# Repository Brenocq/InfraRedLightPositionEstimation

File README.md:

# Light Position Estimation

## Introduction
This project aims to create a neural network to estimate the position of a light emitting object using multiple light sensors.
Firstly the tests are being performed using visible light. In the next step I will use infrared light emitters and receivers.
The main motivation for this project is to allow low cost robots to locate the position of other robots relative to them.

## The Neural Network
Starting from the scenario where there are several robots emitting light and reading the light intensity of the environment. My goal is to get each robot to be able to determine the relative position of another robot using only light sensors. The neural network input will be the reading of each sensor, while the output will be the relative coordinate of the other robot closest to it.

### Training
The training will take place using a camera to detect the relative position of the _light emitting PCB_ relative to the _main PCB with sensors_. After data is collected, the neural network is fed with the values of each sensor and the error is adjusted using the coordinates of the robots.

## Experiments
### First experiment: Visible light

#### Work in progress...

### Installation
```
sudo apt-get install libusb-1.0-0.dev
sudo apt-get install libboost-all-dev
sudo apt-get install cmake

cd LightPositionEstimation/src/Raspberry/lib/Pixy/
rm -r build
cd scripts
./build_libpixyusb.sh
./install_libpixyusb.sh

cd ../../../
rm -r build
./make.sh
```

[Pixymon](https://docs.pixycam.com/wiki/doku.php?id=wiki:v1:installing_pixymon_on_linux)

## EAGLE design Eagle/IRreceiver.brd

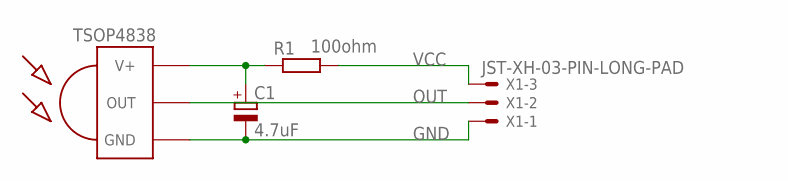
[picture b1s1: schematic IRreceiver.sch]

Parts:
C1: 4.7uF; 153CLV-0405
R1: 100ohm; R0805
U$1: TSOP4838; TSOP18XX
X1: JST-XH-03-PIN-LONG-PAD; JST-XH-03-PACKAGE-LONG-PAD

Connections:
GND: C1.-, U$1.GND, X1.1
unnamed: C1.+, R1.1, U$1.VCC (V+)
OUT: U$1.OUT, X1.2
VCC: R1.2, X1.3

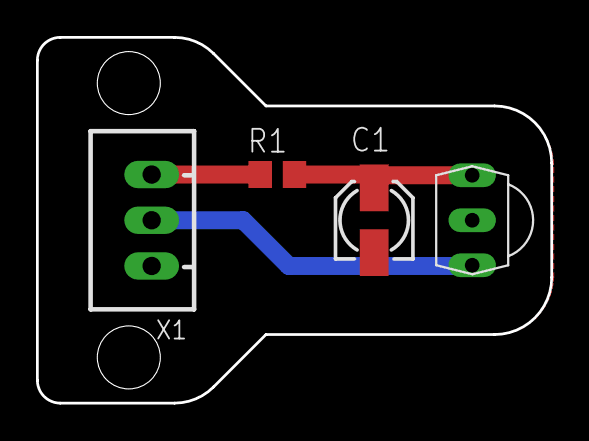
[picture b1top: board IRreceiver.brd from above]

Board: 2 copper layers, 28.6 x 20.3 mm, 4 parts (0 on the bottom side), 4 nets.

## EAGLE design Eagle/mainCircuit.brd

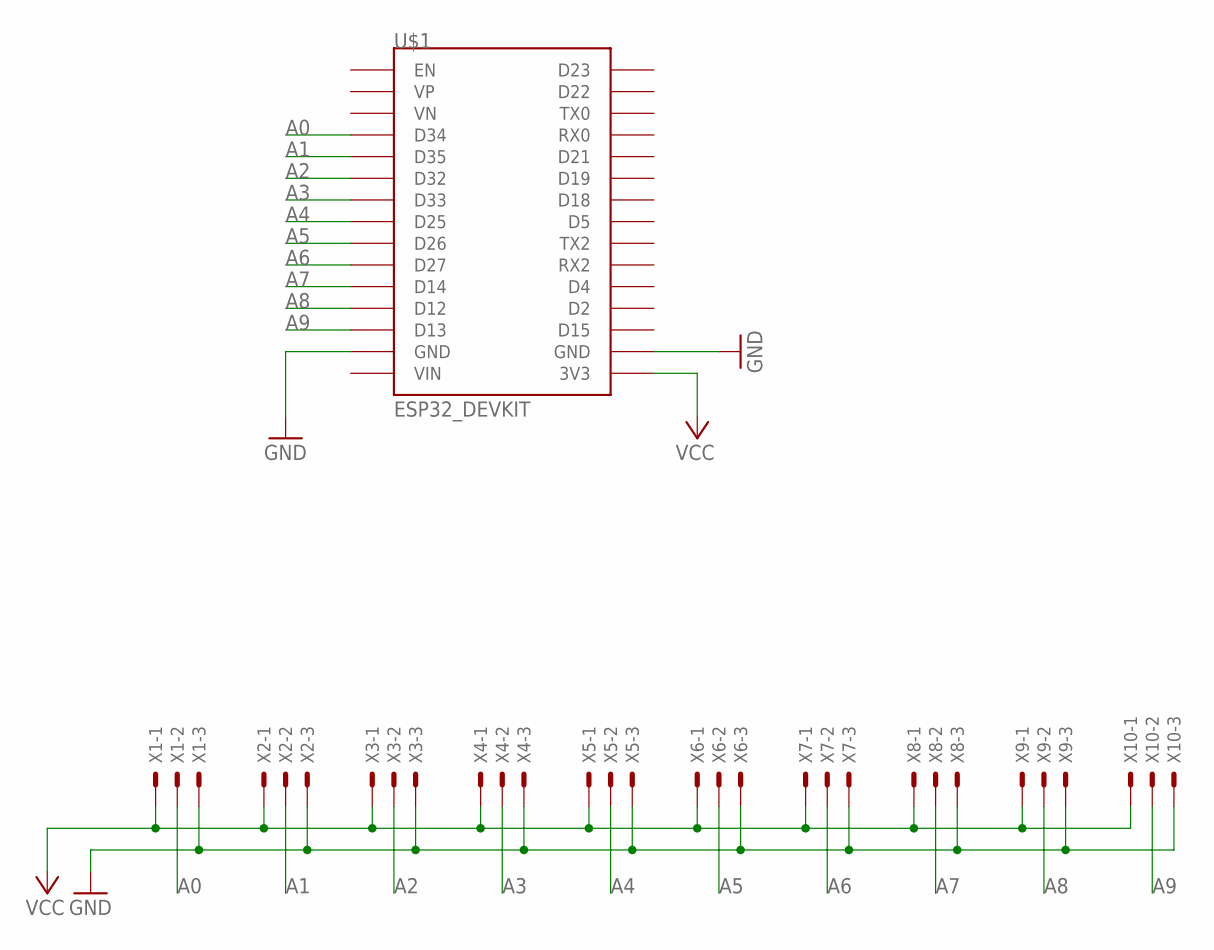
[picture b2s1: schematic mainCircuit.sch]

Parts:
U$1: ESP32_DEVKIT
X1, X2, X3, X4, X5, X6, X7, X8, X9, X10: JST-XH-03-PIN-LONG-PAD; JST-XH-03-PACKAGE-LONG-PAD

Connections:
A0: U$1.D34, X1.2
A1: U$1.D35, X2.2
A2: U$1.D32, X3.2
A3: U$1.D33, X4.2
A4: U$1.D25, X5.2
A5: U$1.D26, X6.2
A6: U$1.D27, X7.2
A7: U$1.D14, X8.2
A8: U$1.D12, X9.2
A9: U$1.D13, X10.2
GND: U$1.GND@1 (GND), U$1.GND@2 (GND), X1.3, X2.3, X3.3, X4.3, X5.3, X6.3, X7.3, X8.3, X9.3, X10.3
VCC: U$1.3V3, X1.1, X2.1, X3.1, X4.1, X5.1, X6.1, X7.1, X8.1, X9.1, X10.1

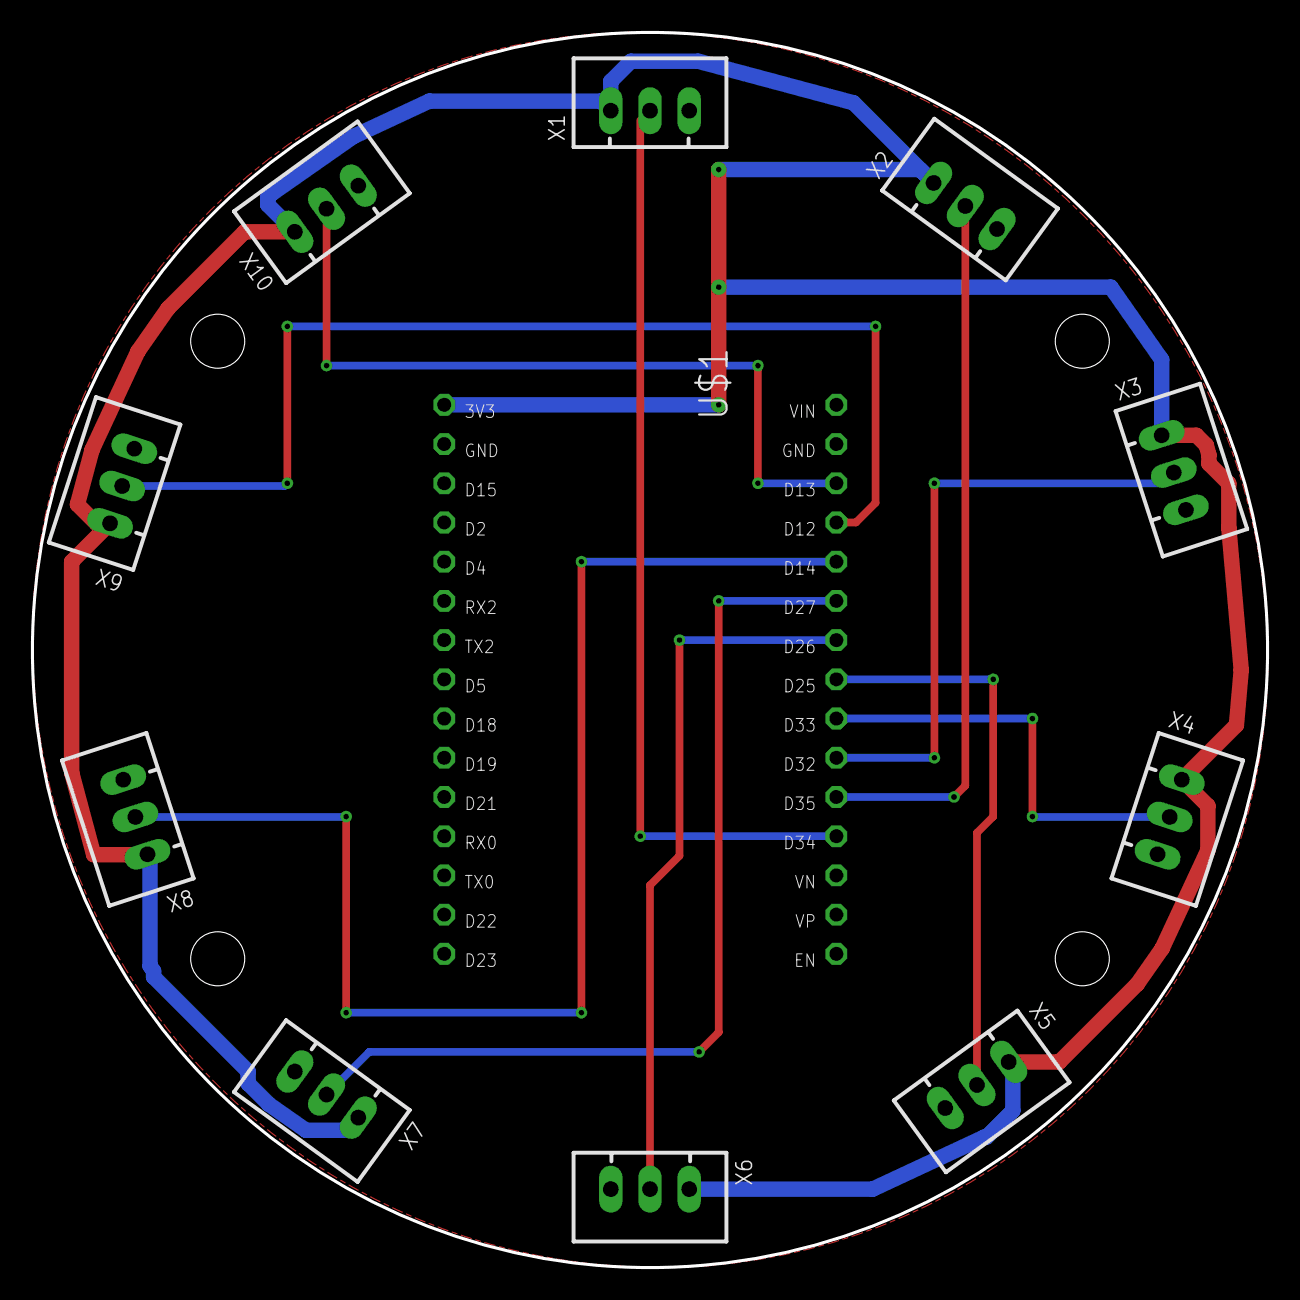
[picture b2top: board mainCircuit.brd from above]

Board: 2 copper layers, 80.0 x 80.0 mm, 11 parts (0 on the bottom side), 12 nets.

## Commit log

2019-08-10 Feat: Eagle files
2019-08-15 Feat: Pixy library
2019-08-15 Refeat: Fix pixy submodule
2019-08-16 Feat: Detect two objects
2019-10-01 Feat: Altium pcb and main structure
2019-10-02 Docs: Explain project
2019-10-16 Create LICENSE
2019-11-02 Feat: Read sensor data with esp-idf
2019-11-02 Real-time plotting
2019-11-02 Feat: Raspberry serial communication
2019-11-02 Auto stash before merge of "master" and "origin/master"
2019-11-03 Add first plot to readme
2019-11-03 Docs: Images first tests LDR circuit
